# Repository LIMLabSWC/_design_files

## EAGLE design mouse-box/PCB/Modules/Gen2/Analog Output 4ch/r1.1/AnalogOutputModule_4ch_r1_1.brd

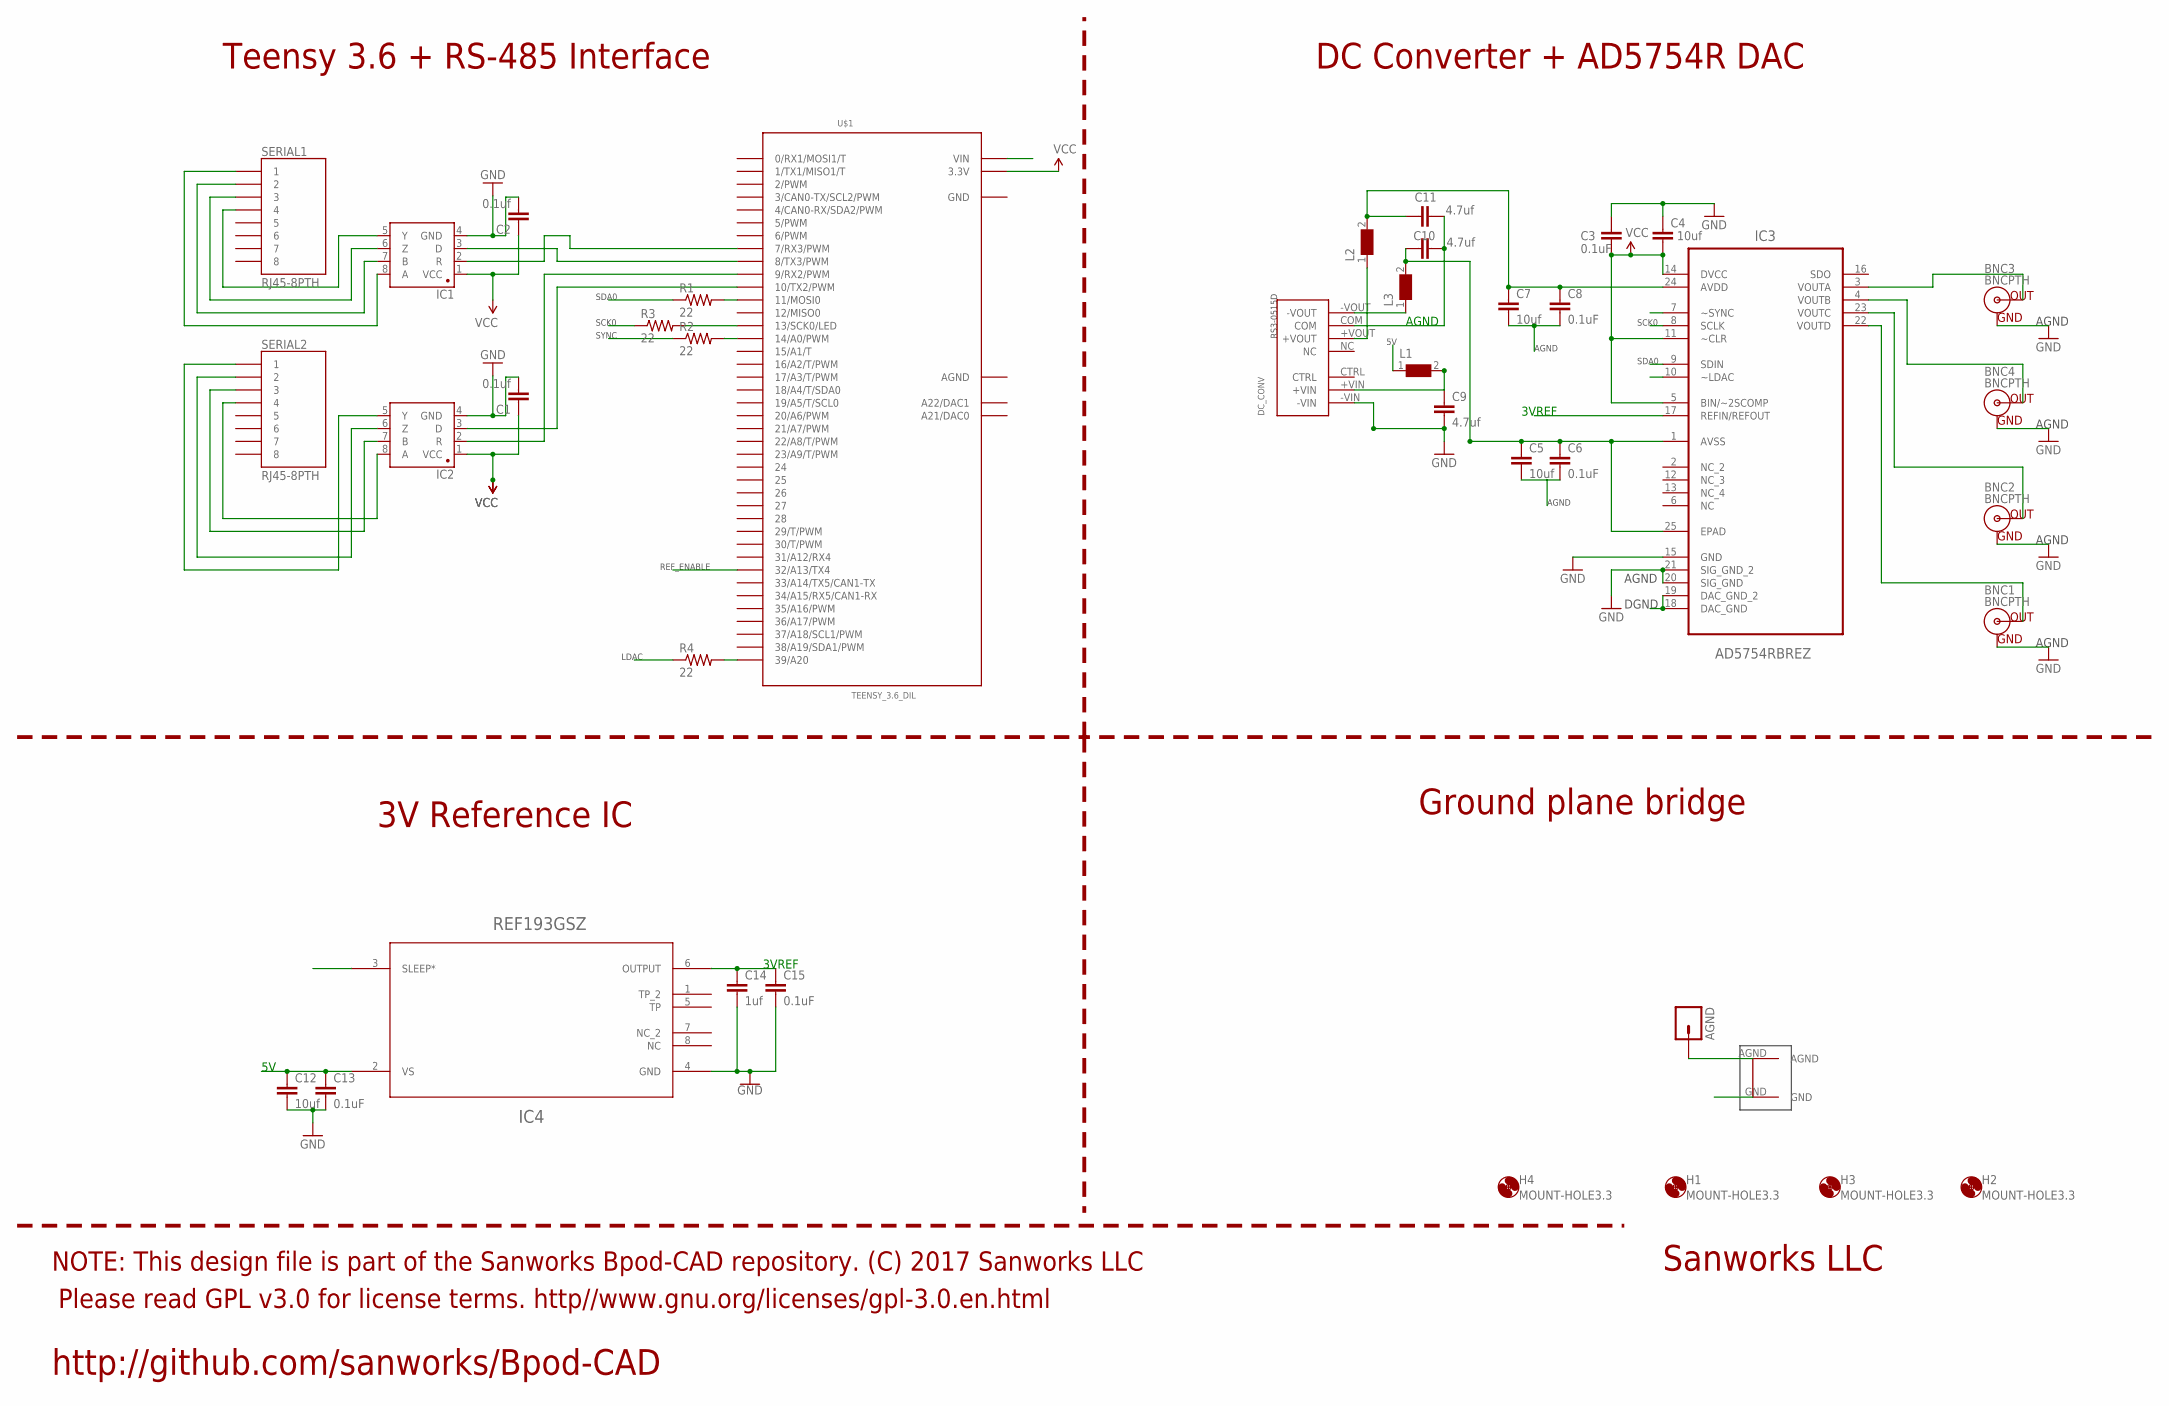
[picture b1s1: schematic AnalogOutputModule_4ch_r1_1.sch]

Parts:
AGND: M01PTH; 1X01
BNC1, BNC2, BNC3, BNC4: BNCPTH; BNC
C1, C2: 0.1uf; 1206@1
C3, C6, C8, C13, C15: 0.1uF; 0805
C4, C5, C7, C12: 10uf; 1206@1
C9, C10, C11: 4.7uf; 1206@1
C14: 1uf; 1206@1
DC_CONV: RS3-0515D
H1, H2, H3, H4: MOUNT-HOLE3.3; 3,3
IC1, IC2: SN65HVD31DR; SO08
IC3: AD5754RBREZ; SOP65P640X120-25N
IC4: REF193GSZ; R_8
L1, L2, L3: WE-CBF-742792118_1206; 1206
R1, R2, R3, R4: 22; 1206
SERIAL1, SERIAL2: RJ45-8PTH; RJ45-8
U$1: TEENSY_3.6_DIL
U$6: GNDPLANESHRT

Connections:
3VREF: C14.1, C15.1, IC3.17 (REFIN/REFOUT), IC4.6 (OUTPUT)
5V: C3.2, C4.2, C12.1, C13.1, IC3.5 (BIN/~2SCOMP), IC3.11 (~CLR), IC3.14 (DVCC), IC4.2 (VS), L1.1, U$1.VIN
AGND: AGND.1, BNC1.GND, BNC2.GND, BNC3.GND, BNC4.GND, C5.2, C6.2, C7.2, C8.2, C10.1, C11.2, DC_CONV.COM, IC3.18 (DAC_GND), IC3.19 (DAC_GND_2), IC3.20 (SIG_GND), IC3.21 (SIG_GND_2), U$1.AGND, U$6.AGND
GND: C1.2, C2.2, C3.1, C4.1, C9.2, C12.2, C13.2, C14.2, C15.2, DC_CONV.-VIN, IC1.4 (GND), IC2.4 (GND), IC3.15 (GND), IC4.4 (GND), U$1.GND, U$1.GND1 (GND), U$6.GND
LDAC: IC3.10 (~LDAC), R4.1
unnamed: IC1.3 (D), U$1.8 (8/TX3/PWM)
unnamed: IC1.2 (R), U$1.7 (7/RX3/PWM)
unnamed: IC2.8 (A), SERIAL2.4
unnamed: IC2.7 (B), SERIAL2.3
unnamed: IC2.6 (Z), SERIAL2.2
unnamed: IC2.5 (Y), SERIAL2.1
unnamed: IC2.3 (D), U$1.10 (10/TX2/PWM)
unnamed: IC2.2 (R), U$1.9 (9/RX2/PWM)
unnamed: BNC3.S (OUT), IC3.3 (VOUTA)
unnamed: BNC4.S (OUT), IC3.4 (VOUTB)
unnamed: BNC2.S (OUT), IC3.23 (VOUTC)
unnamed: BNC1.S (OUT), IC3.22 (VOUTD)
unnamed: R1.2, U$1.11 (11/MOSI0)
unnamed: R3.2, U$1.13 (13/SCK0/LED)
unnamed: DC_CONV.-VOUT, L3.1
unnamed: DC_CONV.+VOUT, L2.1
unnamed: R2.2, U$1.14/A0 (14/A0/PWM)
unnamed: R4.2, U$1.39/A20
unnamed: IC1.8 (A), SERIAL1.1
unnamed: IC1.7 (B), SERIAL1.2
unnamed: IC1.6 (Z), SERIAL1.3
unnamed: IC1.5 (Y), SERIAL1.4
unnamed: C7.1, C8.1, C10.2, IC3.24 (AVDD), L2.2
unnamed: C9.1, DC_CONV.+VIN, L1.2
REF_ENABLE: IC4.3 (SLEEP*), U$1.32/A13 (32/A13/TX4)
SCK0: IC3.8 (SCLK), R3.1
SDA0: IC3.9 (SDIN), R1.1
SYNC: IC3.7 (~SYNC), R2.1
VCC: C1.1, C2.1, IC1.1 (VCC), IC2.1 (VCC), U$1.3.3V, U$1.3.3V3 (3.3V)
VSS: C5.1, C6.1, C11.1, IC3.1 (AVSS), IC3.25 (EPAD), L3.2

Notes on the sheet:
AGND
SCK0
SDA0
DGND
SYNC
LDAC
3VREF
REF_ENABLE
Teensy 3.6 + RS-485 Interface
DC Converter + AD5754R DAC
3V Reference IC
Ground plane bridge
Please read GPL v3.0 for license terms. http//www.gnu.org/licenses/gpl-3.0.en.html
NOTE: This design file is part of the Sanworks Bpod-CAD repository. (C) 2017 Sanworks LLC
Sanworks LLC
http://github.com/sanworks/Bpod-CAD

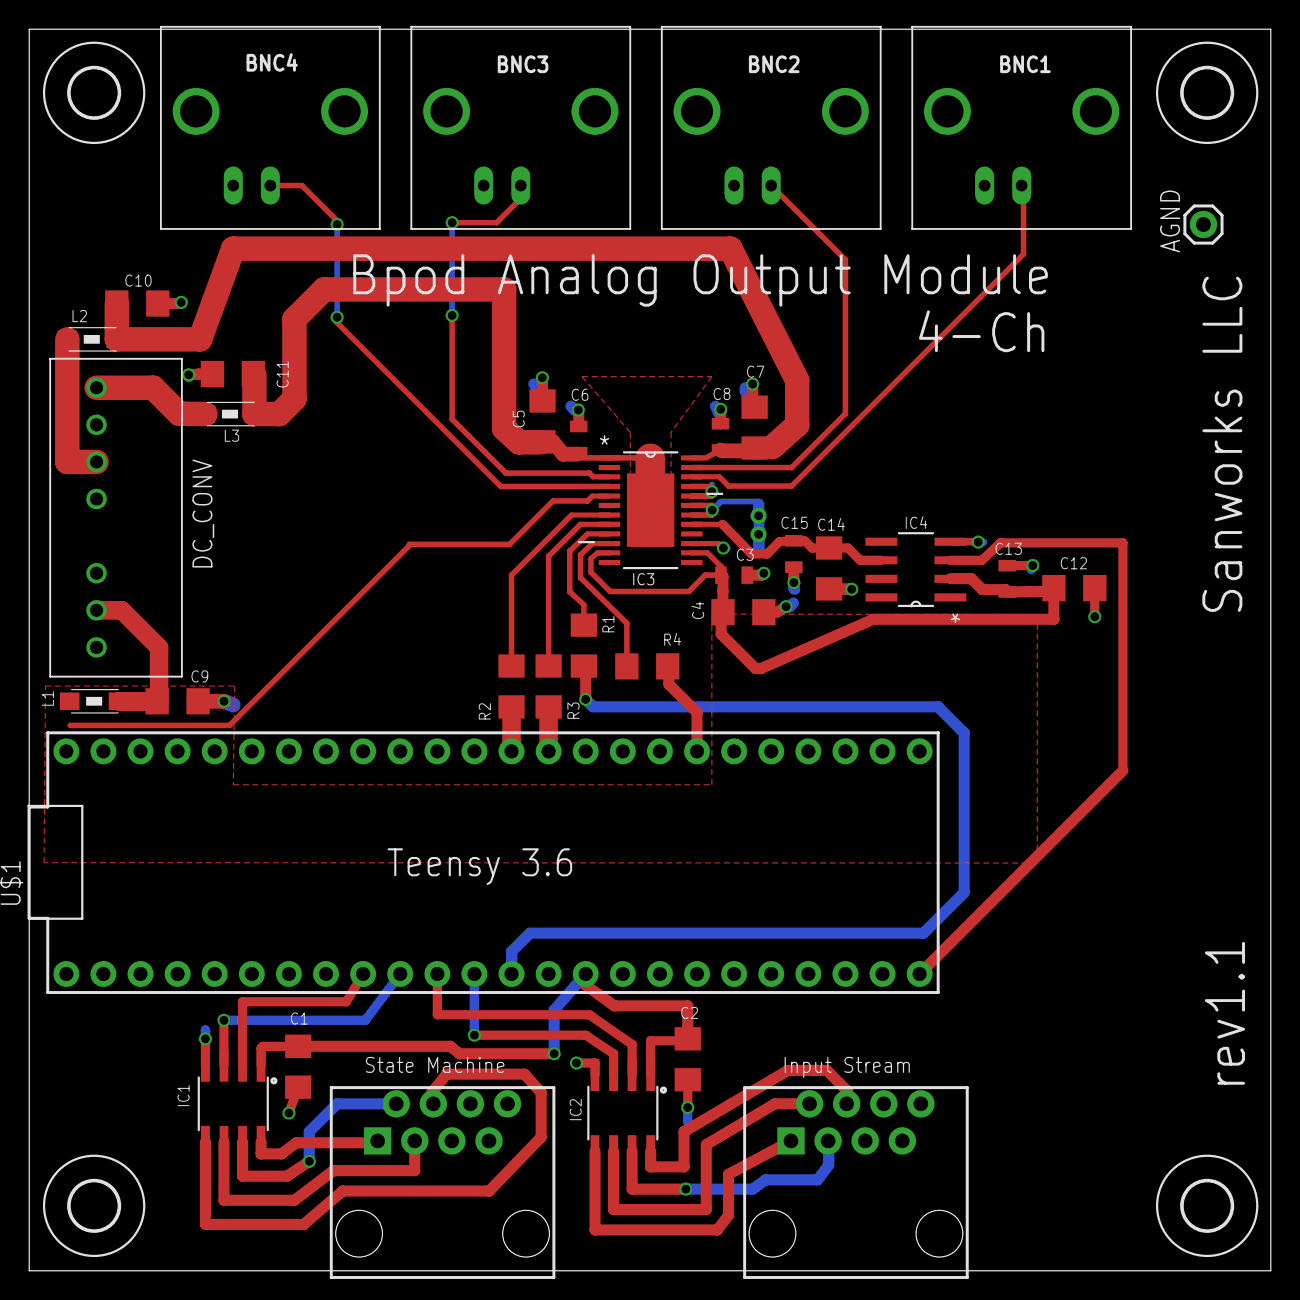
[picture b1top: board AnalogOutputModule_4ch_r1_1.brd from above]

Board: 2 copper layers, 85.0 x 85.0 mm, 40 parts (0 on the bottom side), 35 nets.

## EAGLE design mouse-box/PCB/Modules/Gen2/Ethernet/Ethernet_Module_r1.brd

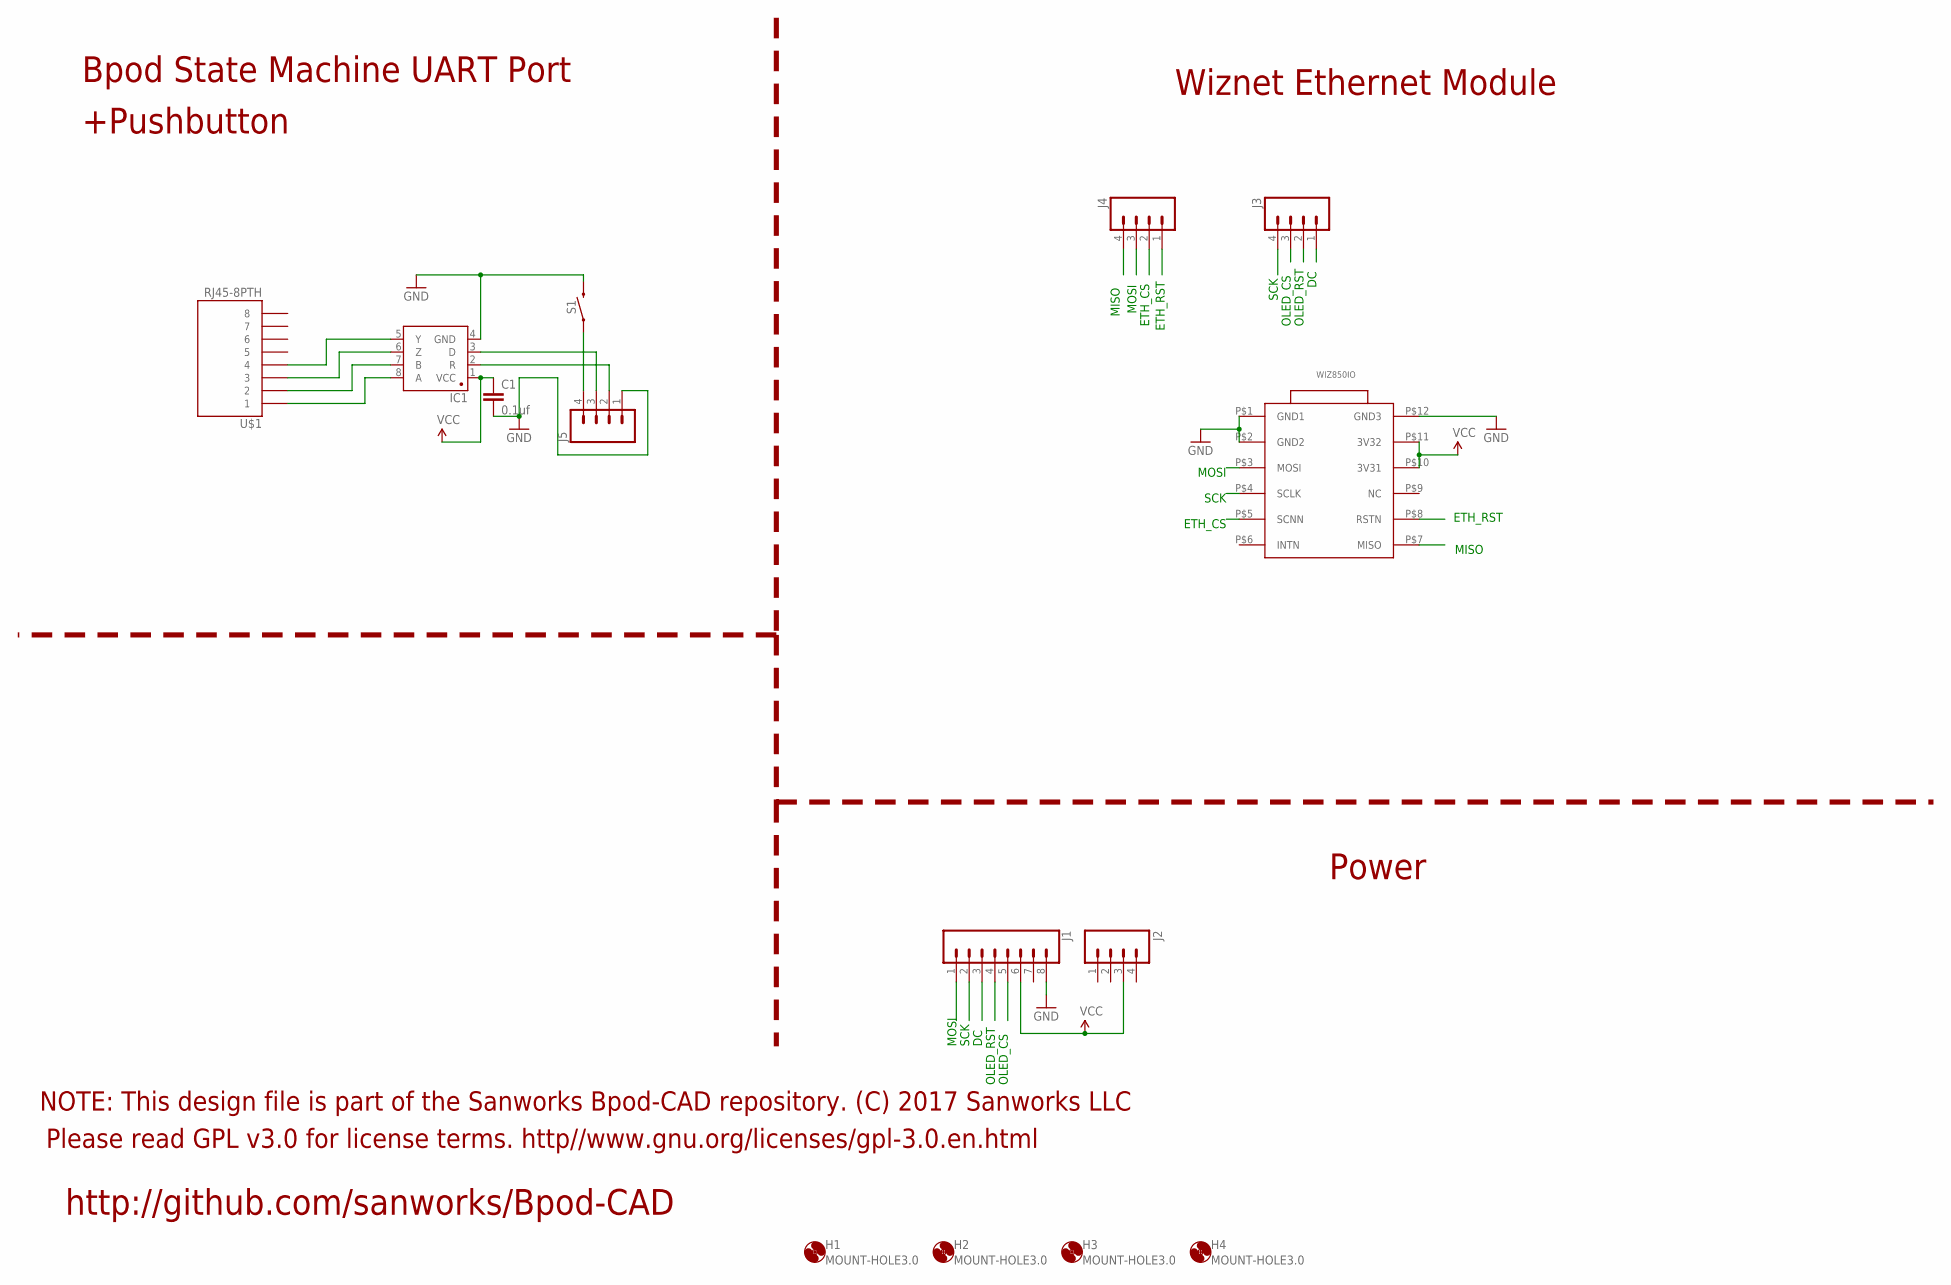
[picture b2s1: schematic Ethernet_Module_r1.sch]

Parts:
C1: 0.1uf; 1206@1
H1, H2, H3, H4: MOUNT-HOLE3.0; 3,0
IC1: SN65HVD31DR; SO08
J1: CONN_08LONGPADS; 1X08_LONGPADS
J2, J3, J4, J5: M04PTH; 1X04
S1: MOMENTARY-SWITCH-SPST-SMD-5.2MM; TACTILE_SWITCH_SMD_5.2MM
U$1: RJ45-8PTH; RJ45-8
WIZ850IO: WIZ850IO

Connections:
DC: J1.3, J3.1
ETH_CS: J4.2, WIZ850IO.P$5 (SCNN)
ETH_RST: J4.1, WIZ850IO.P$8 (RSTN)
GND: C1.2, IC1.4 (GND), J1.8, J5.1, S1.3 (2), WIZ850IO.P$1 (GND1), WIZ850IO.P$2 (GND2), WIZ850IO.P$12 (GND3)
MISO: J4.4, WIZ850IO.P$7 (MISO)
MOSI: J1.1, J4.3, WIZ850IO.P$3 (MOSI)
unnamed: J5.4, S1.1
unnamed: IC1.8 (A), U$1.1
unnamed: IC1.7 (B), U$1.2
unnamed: IC1.6 (Z), U$1.3
unnamed: IC1.5 (Y), U$1.4
OLED_CS: J1.5, J3.3
OLED_RST: J1.4, J3.2
RX1: IC1.2 (R), J5.2
SCK: J1.2, J3.4, WIZ850IO.P$4 (SCLK)
TX1: IC1.3 (D), J5.3
VCC: C1.1, IC1.1 (VCC), J1.6, J2.3, WIZ850IO.P$10 (3V31), WIZ850IO.P$11 (3V32)

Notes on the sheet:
Bpod State Machine UART Port
Wiznet Ethernet Module
Power
Please read GPL v3.0 for license terms. http//www.gnu.org/licenses/gpl-3.0.en.html
NOTE: This design file is part of the Sanworks Bpod-CAD repository. (C) 2017 Sanworks LLC
http://github.com/sanworks/Bpod-CAD
MOSI
SCK
OLED_RST
OLED_CS
MISO
ETH_CS
ETH_RST
+Pushbutton

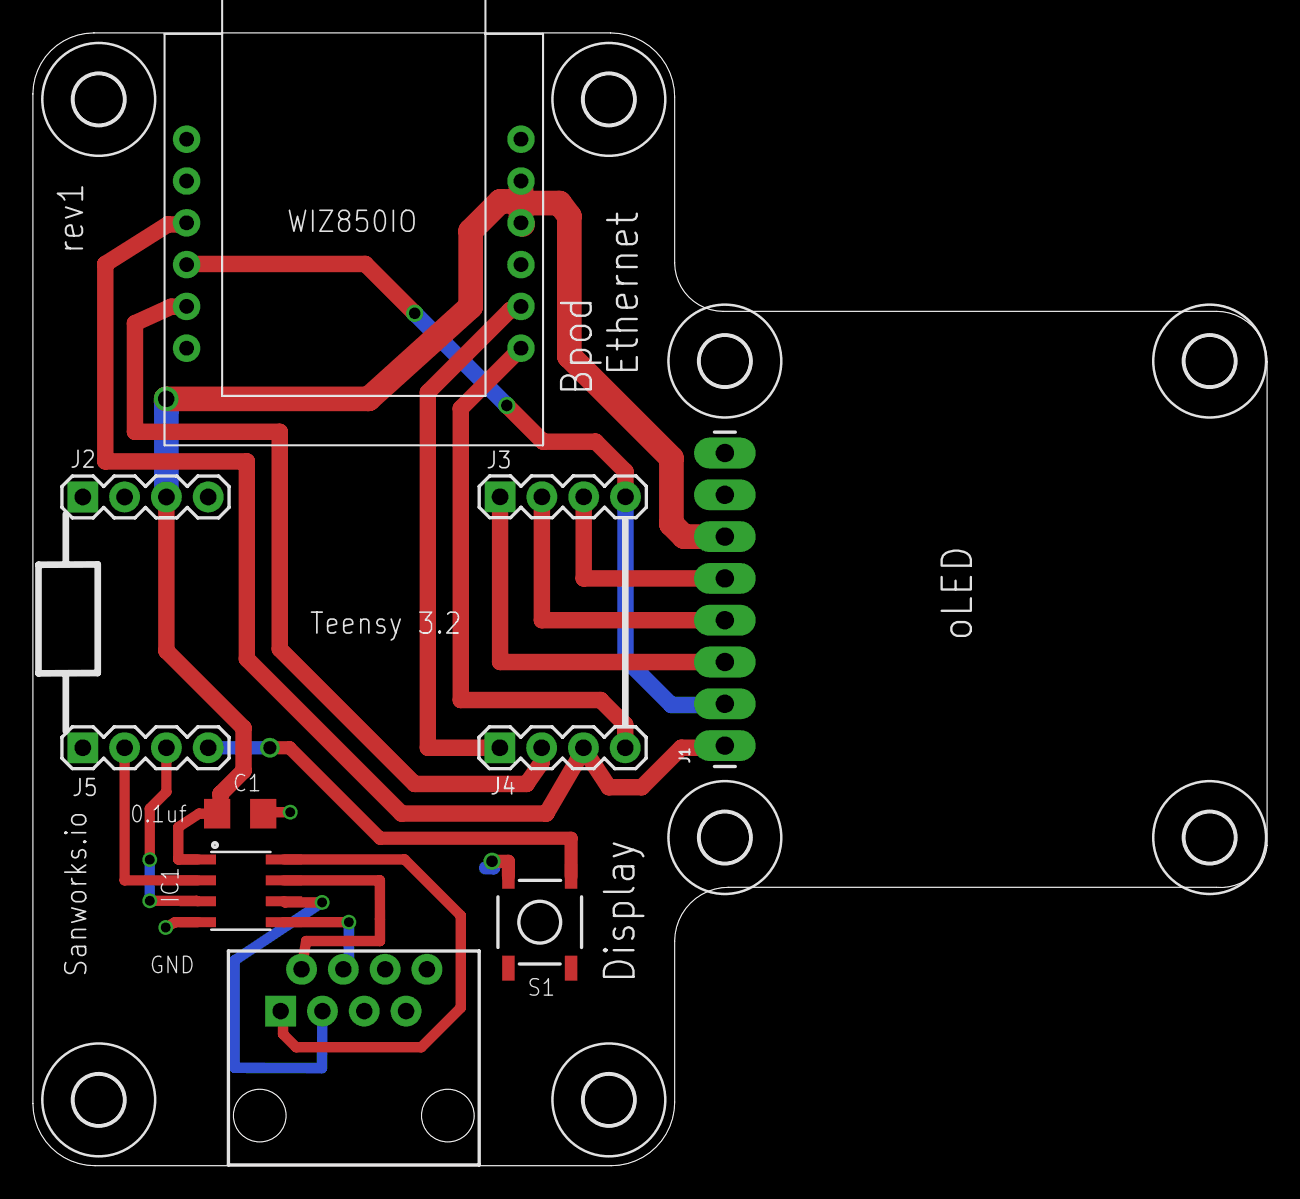
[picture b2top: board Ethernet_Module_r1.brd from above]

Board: 2 copper layers, 75.0 x 68.8 mm, 18 parts (0 on the bottom side), 17 nets.

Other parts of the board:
H5, H6, H7, H8: MOUNT-HOLE3.0; 3,0

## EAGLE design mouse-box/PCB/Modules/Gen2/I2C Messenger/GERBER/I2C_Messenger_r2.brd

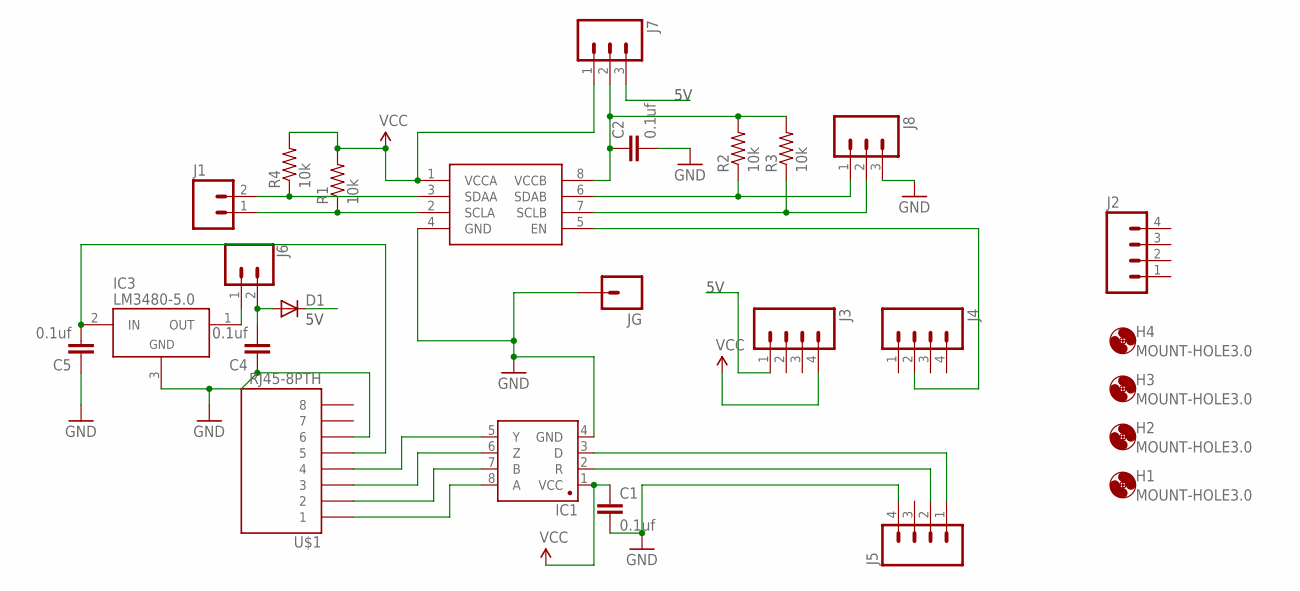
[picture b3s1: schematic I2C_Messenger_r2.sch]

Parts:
C1, C2, C4, C5: 0.1uf; 1206
D1: MBR0520LT; SOD123
H1, H2, H3, H4: MOUNT-HOLE3.0; 3,0
IC1: SN65HVD31DR; SO08
IC2: PCA9517; SO-08
IC3: LM3480-5.0; SOT-23-3
J1: M02PTH; 1X02@1
J2, J3, J4, J5: M04PTH; 1X04
J6: CONN_02; 1X02
J7: M03PTH; 1X03
J8: M03SCREW_LOCK; SCREWTERMINAL-3.5MM-3_LOCK.007S
JG: M01PTH; 1X01
R1, R2, R3, R4: 10k; 1206
U$1: RJ45-8PTH; RJ45-8

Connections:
5V: D1.C, J3.1, J7.3
GND: C1.2, C2.2, C4.1, C5.1, IC1.4 (GND), IC2.4 (GND), IC3.3 (GND), J5.4, J8.3, JG.1, U$1.6
unnamed: C4.2, D1.A, J6.2
unnamed: IC3.1 (OUT), J6.1
unnamed: IC1.3 (D), J5.1
unnamed: IC2.2 (SCLA), J1.1, R1.1
unnamed: IC1.2 (R), J5.2
unnamed: IC1.8 (A), U$1.1
unnamed: IC1.7 (B), U$1.2
unnamed: IC1.6 (Z), U$1.3
unnamed: IC1.5 (Y), U$1.4
unnamed: IC2.3 (SDAA), J1.2, R4.1
unnamed: C2.1, IC2.8 (VCCB), J7.2, R2.2, R3.2
unnamed: IC2.5 (EN), J4.2
unnamed: IC2.6 (SDAB), J8.1, R2.1
unnamed: IC2.7 (SCLB), J8.2, R3.1
unnamed: C5.2, IC3.2 (IN), U$1.5
VCC: C1.1, IC1.1 (VCC), IC2.1 (VCCA), J3.4, J7.1, R1.2, R4.2

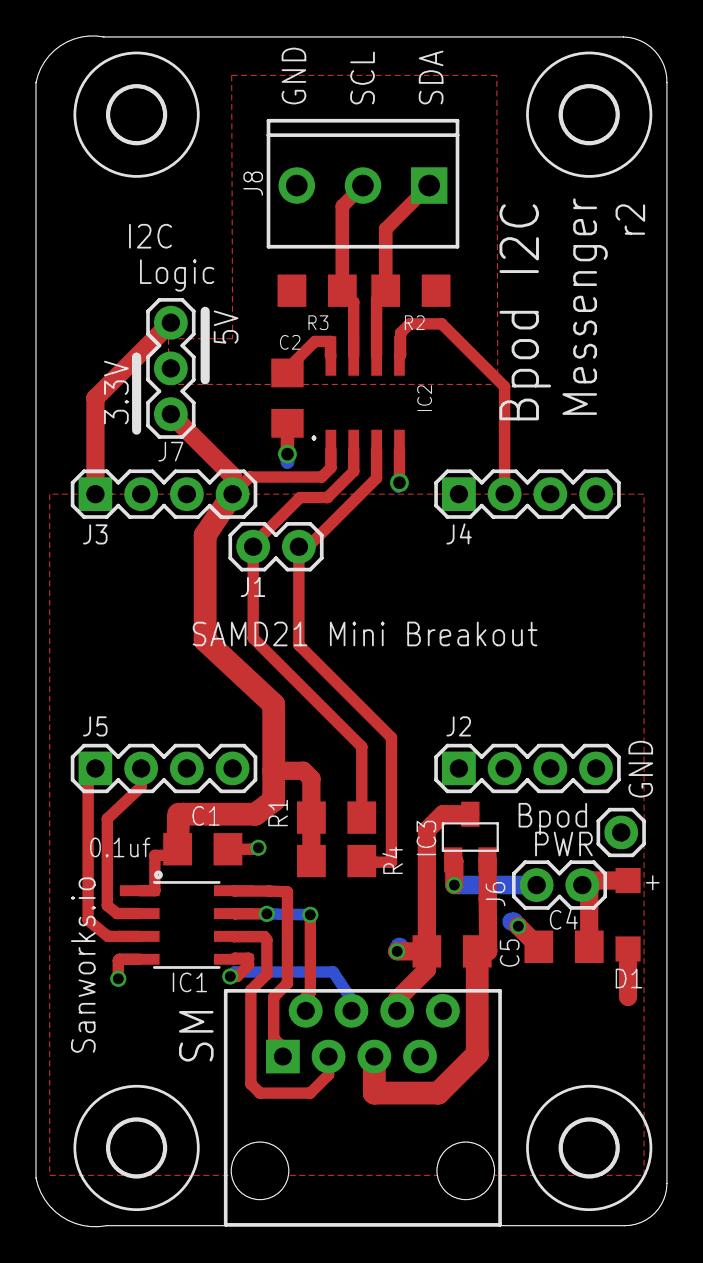
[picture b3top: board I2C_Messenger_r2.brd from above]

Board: 2 copper layers, 35.1 x 66.1 mm, 26 parts (0 on the bottom side), 18 nets.

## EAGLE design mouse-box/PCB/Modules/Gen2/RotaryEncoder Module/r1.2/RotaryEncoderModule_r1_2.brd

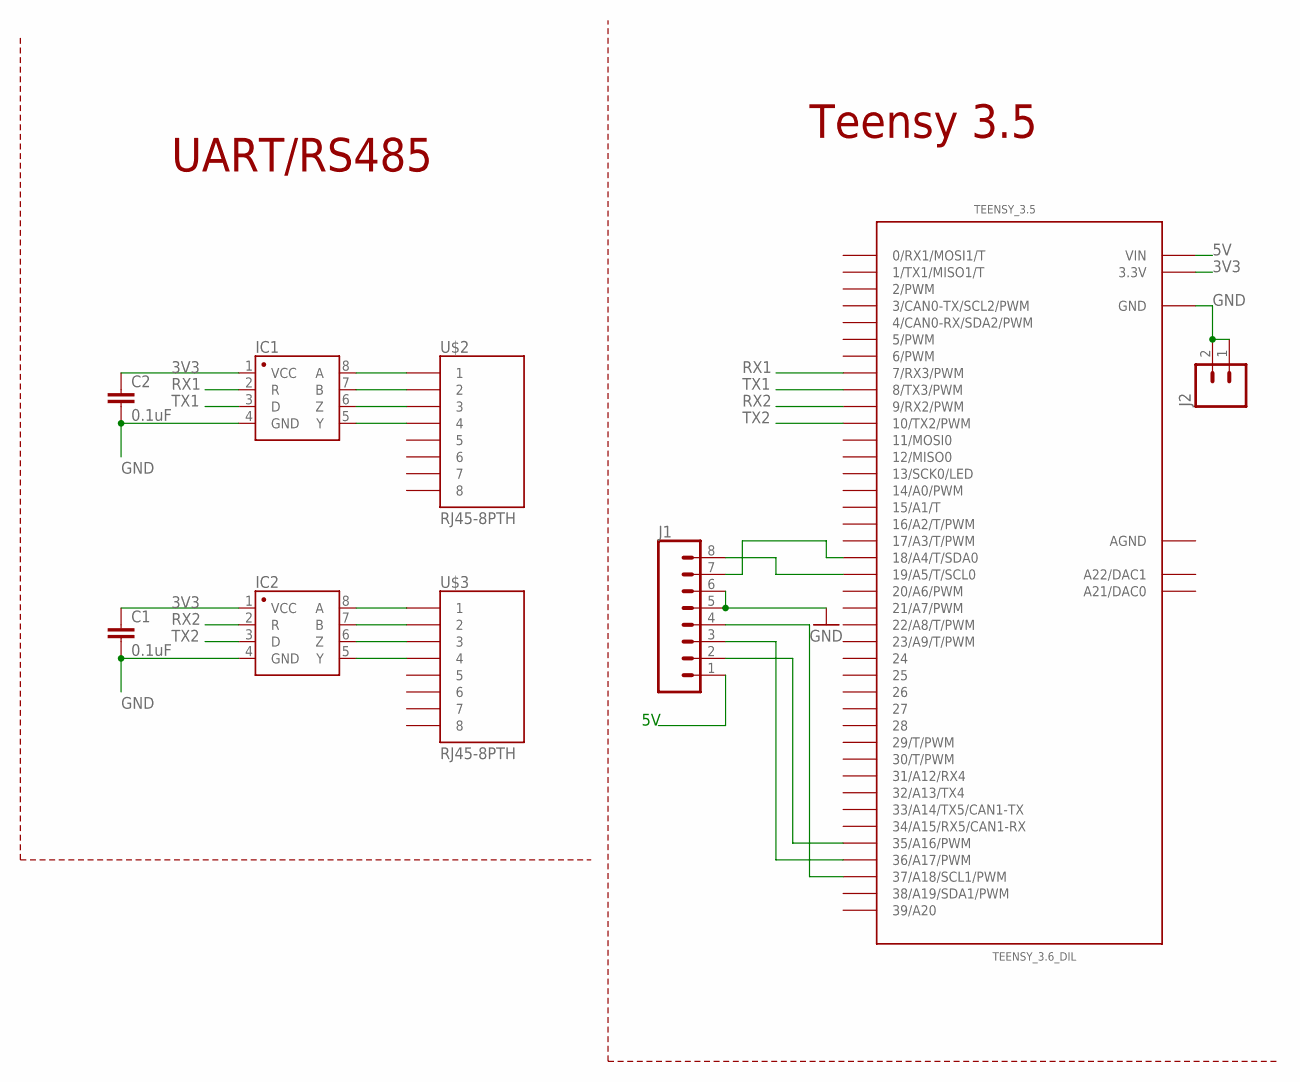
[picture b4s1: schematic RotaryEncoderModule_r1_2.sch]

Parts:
C1, C2: 0.1uF; 1206
IC1, IC2: SN65HVD31DR; SO08
J1: CONN_083.5MM-8; SCREWTERMINAL-3.5MM-8
J2: M023.5MM; SCREWTERMINAL-3.5MM-2
TEENSY_3.5: TEENSY_3.6_DIL
U$2, U$3: RJ45-8PTH; RJ45-8

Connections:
3V3: C1.1, C2.1, IC1.1 (VCC), IC2.1 (VCC), TEENSY_3.5.3.3V, TEENSY_3.5.3.3V3 (3.3V)
5V: J1.1, TEENSY_3.5.VIN
AGND: TEENSY_3.5.AGND
GND: C1.2, C2.2, IC1.4 (GND), IC2.4 (GND), J1.5, J1.6, J2.1, J2.2, TEENSY_3.5.GND, TEENSY_3.5.GND1 (GND)
unnamed: IC1.6 (Z), U$2.3
unnamed: IC1.8 (A), U$2.1
unnamed: IC1.5 (Y), U$2.4
unnamed: IC1.7 (B), U$2.2
unnamed: IC2.6 (Z), U$3.3
unnamed: IC2.5 (Y), U$3.4
unnamed: IC2.8 (A), U$3.1
unnamed: IC2.7 (B), U$3.2
unnamed: J1.8, TEENSY_3.5.19/A5 (19/A5/T/SCL0)
unnamed: J1.7, TEENSY_3.5.18/A4 (18/A4/T/SDA0)
unnamed: J1.2, TEENSY_3.5.35/A16 (35/A16/PWM)
unnamed: J1.3, TEENSY_3.5.36/A17 (36/A17/PWM)
unnamed: J1.4, TEENSY_3.5.37/A18 (37/A18/SCL1/PWM)
RX1: IC1.2 (R), TEENSY_3.5.7 (7/RX3/PWM)
RX2: IC2.2 (R), TEENSY_3.5.9 (9/RX2/PWM)
TX1: IC1.3 (D), TEENSY_3.5.8 (8/TX3/PWM)
TX2: IC2.3 (D), TEENSY_3.5.10 (10/TX2/PWM)

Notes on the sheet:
Teensy 3.5
UART/RS485

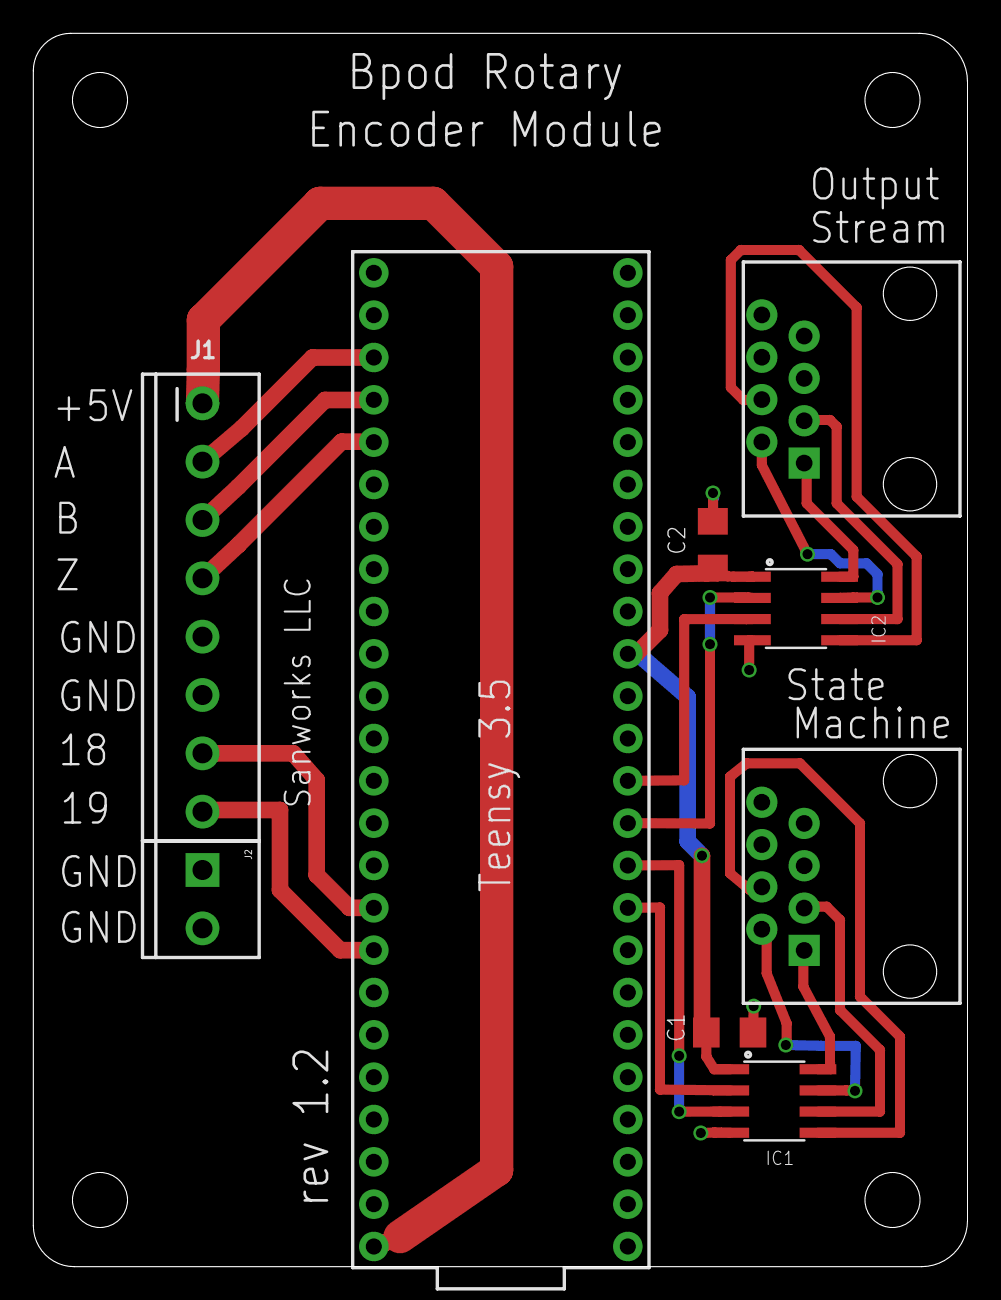
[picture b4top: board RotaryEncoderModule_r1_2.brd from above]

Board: 2 copper layers, 56.0 x 74.0 mm, 13 parts (0 on the bottom side), 20 nets.

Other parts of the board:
U$5, U$6, U$7, U$8: STAND-OFF

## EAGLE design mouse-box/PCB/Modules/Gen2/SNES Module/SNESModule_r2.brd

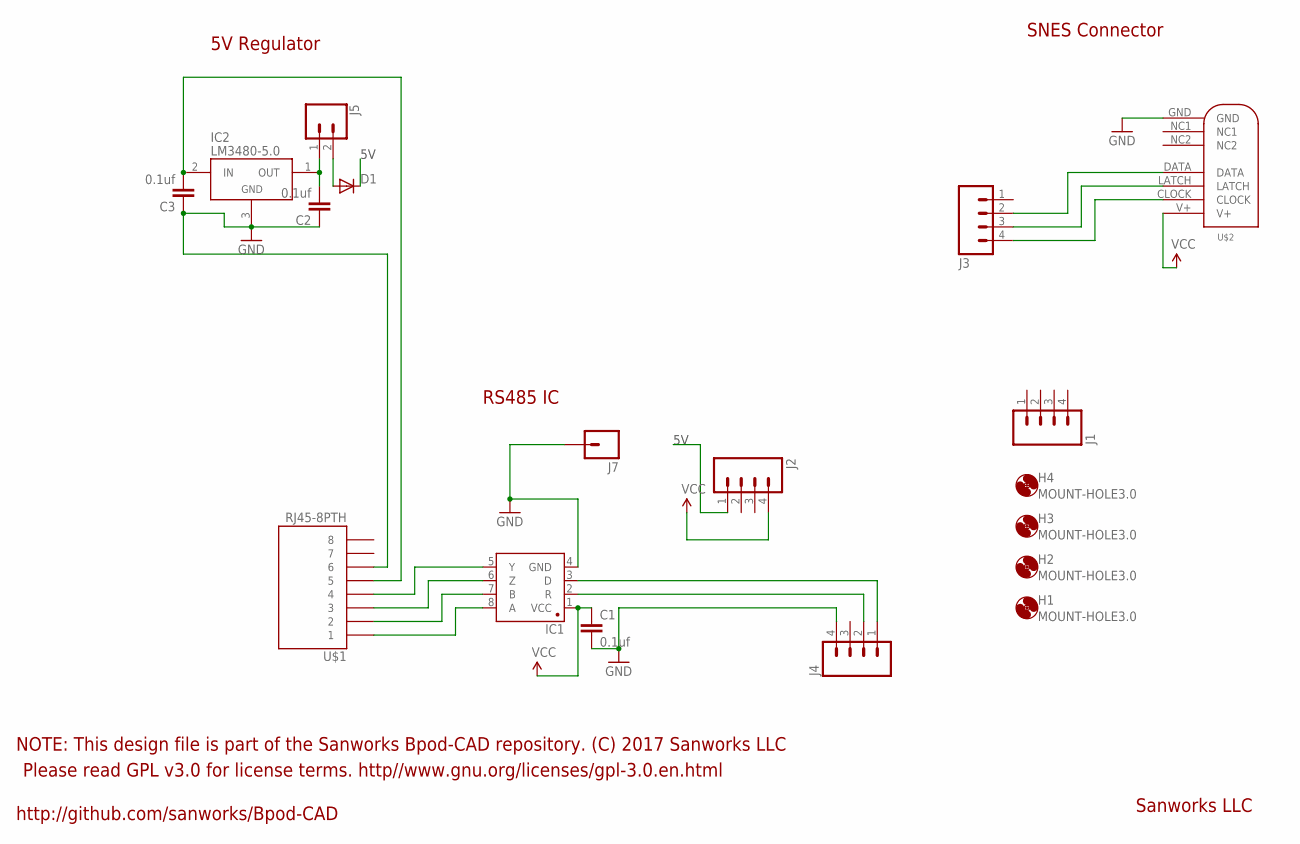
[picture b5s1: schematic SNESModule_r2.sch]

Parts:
C1, C2, C3: 0.1uf; 1206
D1: MBR0520LT; SOD123
H1, H2, H3, H4: MOUNT-HOLE3.0; 3,0
IC1: SN65HVD31DR; SO08
IC2: LM3480-5.0; SOT-23-3
J1, J2, J3, J4: M04PTH; 1X04
J5: CONN_02; 1X02
J7: M01PTH; 1X01
U$1: RJ45-8PTH; RJ45-8
U$2: SNES_CONNECTOR

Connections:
5V: D1.C, J2.1
GND: C1.2, C2.1, C3.1, IC1.4 (GND), IC2.3 (GND), J4.4, J7.1, U$1.6, U$2.GND
unnamed: J3.2, U$2.DATA
unnamed: J3.3, U$2.LATCH
unnamed: J3.4, U$2.CLOCK
unnamed: IC1.3 (D), J4.1
unnamed: C2.2, IC2.1 (OUT), J5.1
unnamed: IC1.2 (R), J4.2
unnamed: IC1.8 (A), U$1.1
unnamed: IC1.7 (B), U$1.2
unnamed: IC1.6 (Z), U$1.3
unnamed: IC1.5 (Y), U$1.4
unnamed: D1.A, J5.2
unnamed: C3.2, IC2.2 (IN), U$1.5
VCC: C1.1, IC1.1 (VCC), J2.4, U$2.V+

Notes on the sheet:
Please read GPL v3.0 for license terms. http//www.gnu.org/licenses/gpl-3.0.en.html
NOTE: This design file is part of the Sanworks Bpod-CAD repository. (C) 2017 Sanworks LLC
http://github.com/sanworks/Bpod-CAD
Sanworks LLC
SNES Connector
5V Regulator
RS485 IC

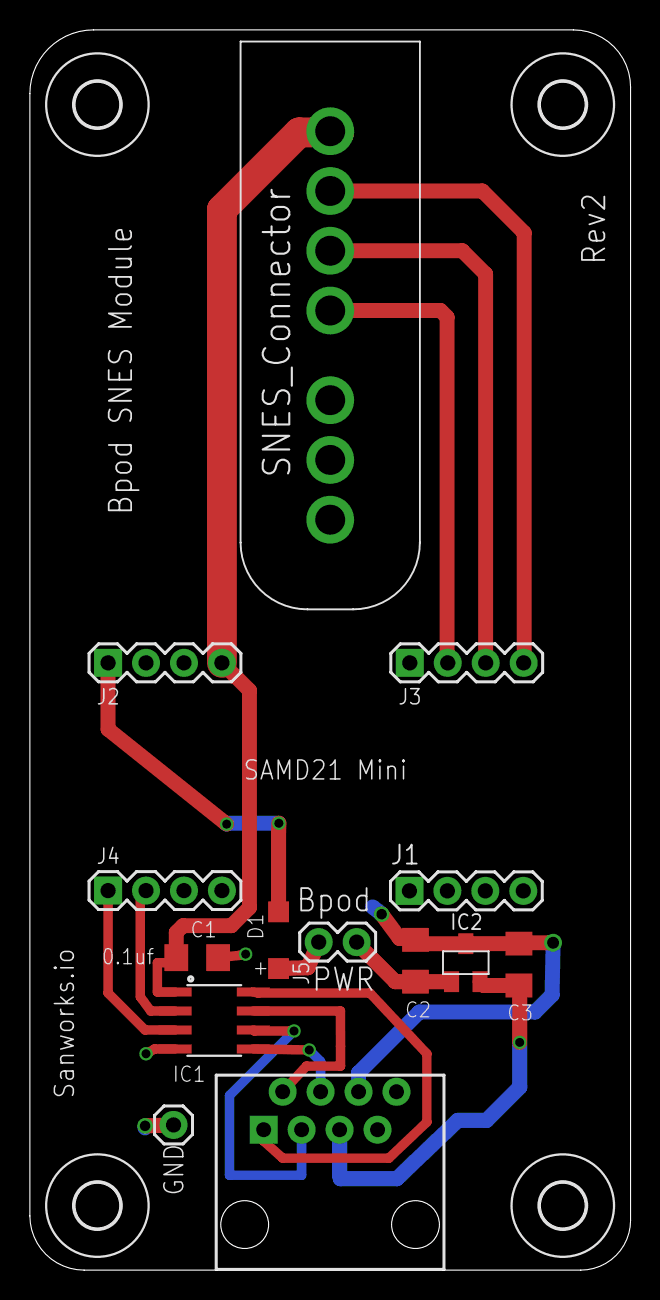
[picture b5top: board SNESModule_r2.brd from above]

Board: 2 copper layers, 40.2 x 83.0 mm, 18 parts (0 on the bottom side), 15 nets.

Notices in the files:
parts and their libraries:
SparkFun-Capacitors: Licensing: Creative Commons ShareAlike 4.0 International - https://creativecommons.org/licenses/by-sa/4.0
SparkFun: Licensing: CC v3.0 Share-Alike You are welcome to use this library for commercial purposes.
